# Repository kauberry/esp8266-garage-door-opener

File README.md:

# esp8266-garage-door-opener
An IoT garage door opener using MQTT for status reporting and web api's for control functions

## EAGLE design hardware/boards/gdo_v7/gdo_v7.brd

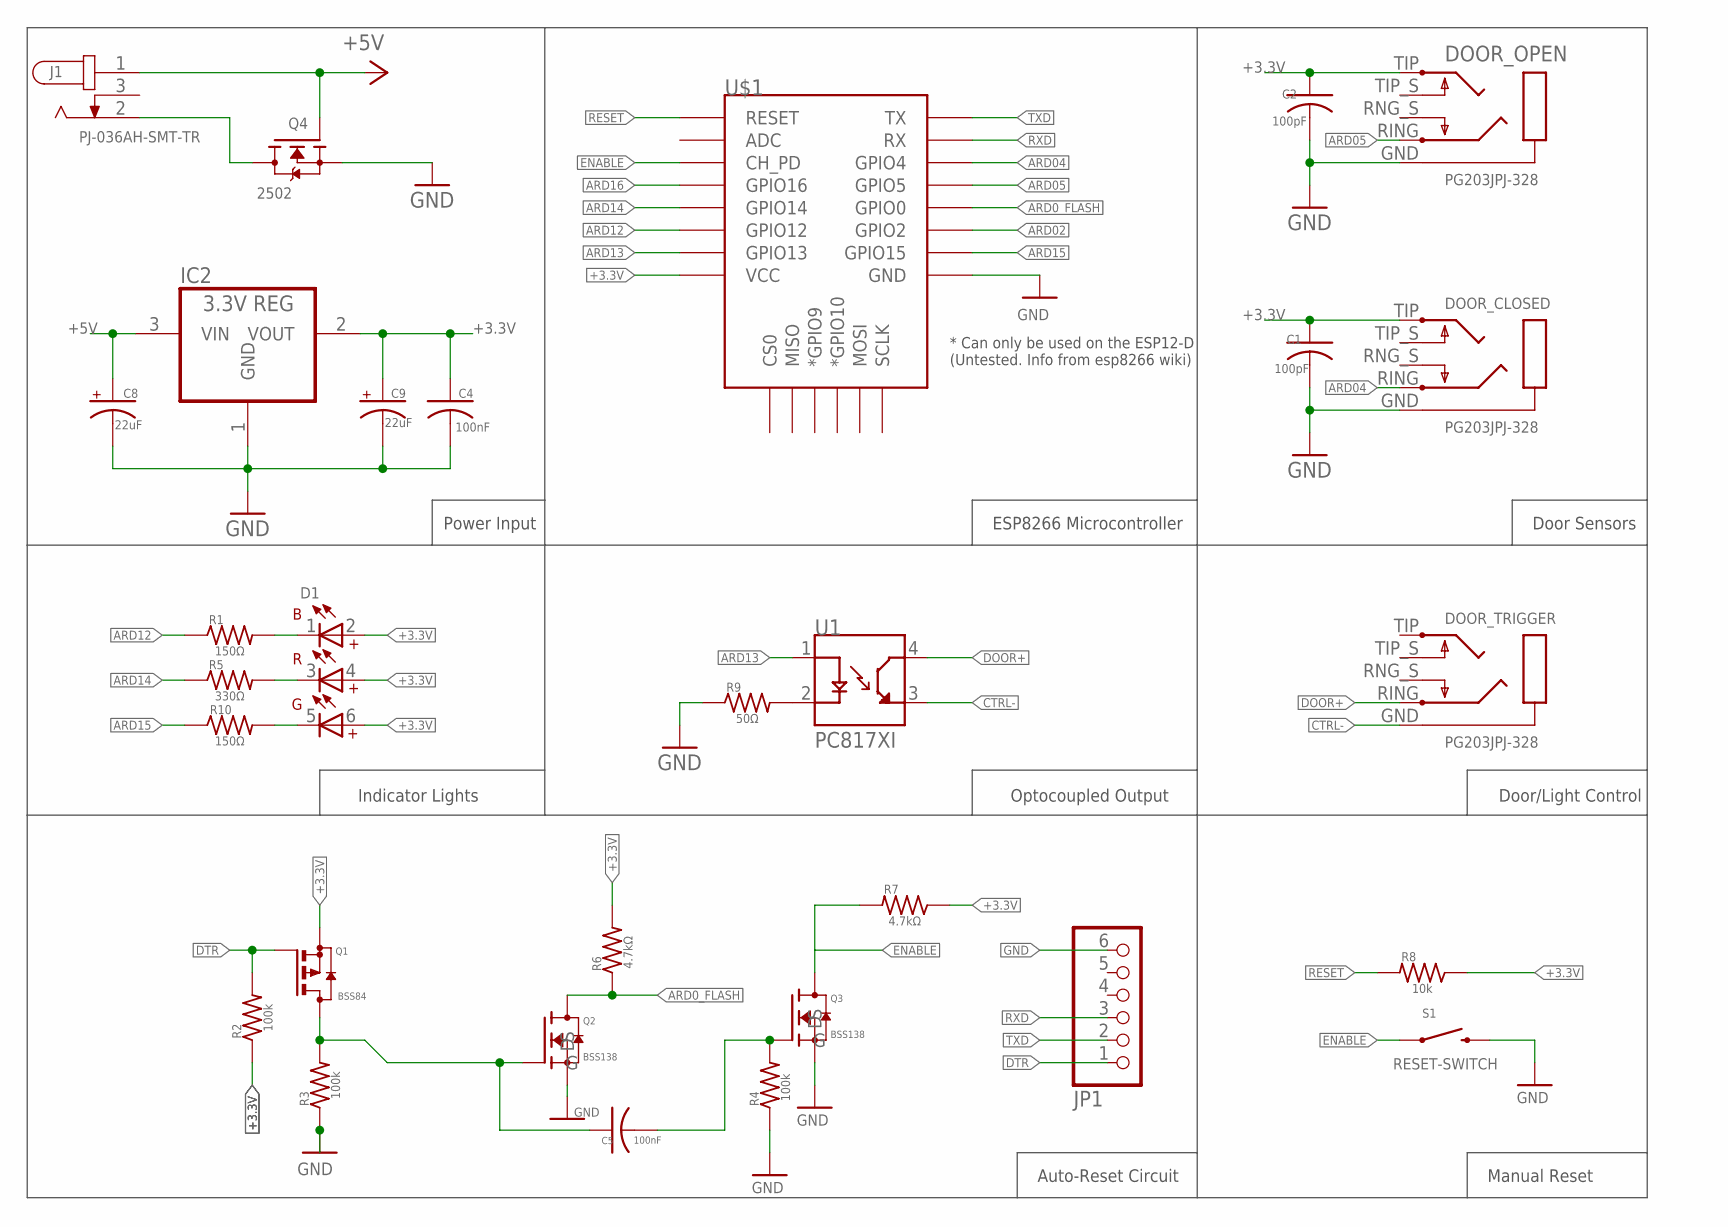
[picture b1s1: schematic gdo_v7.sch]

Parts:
C1, C2: 100pF; C0805
C4, C5: 100nF; C0805
C8, C9: 22uF; EIA3216
D1: WL-SFTW_5050_PLCC6_150505M173300; WL-SFTW_5050_PLCC6
DOOR_CLOSED: PG203JPJ-328; PG203J
DOOR_OPEN: PG203JPJ-328; PG203J
DOOR_TRIGGER: PG203JPJ-328; PG203J
IC2: 3.3V REG; SOT223
J1: PJ-036AH-SMT-TR; CUI_PJ-036AH-SMT-TR
JP1: PINHD-1X6; 1X06
Q1: BSS84; SOT23
Q2, Q3: BSS138
Q4: 2502; SOT23
R1, R10: 150Ω; R0805
R2, R3, R4: 100k; R0805
R5: 330Ω; R0805
R6, R7: 4.7kΩ; R0805
R8: 10k; R0805
R9: 50Ω; R0805
S1: RESET-SWITCH; TACTILE-SWITCH-1101NE
U1: PC817XI; SOIC254P975X460-4N
U$1: ESP12ESMD; ESP12E-SMD

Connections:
+3.3V: C1.1, C2.1, C4.1, C9.A (+), D1.2, D1.4, D1.6, DOOR_CLOSED.TIP (5), DOOR_OPEN.TIP (5), IC2.2 (VOUT), Q1.2 (S), R2.1, R6.2, R7.1, R8.1, U$1.VCC
+5V: C8.A (+), IC2.3 (VIN), J1.1, Q4.1 (G)
ARD0_FLASH: Q2.D, R6.1, U$1.GPIO0
ARD02: U$1.GPIO2
ARD04: DOOR_CLOSED.RING (2), U$1.GPIO4
ARD05: DOOR_OPEN.RING (2), U$1.GPIO5
ARD12: R1.1, U$1.GPIO12
ARD13: U1.1 (A), U$1.GPIO13
ARD14: R5.1, U$1.GPIO14
ARD15: R10.1, U$1.GPIO15
ARD16: U$1.GPIO16
CTRL-: DOOR_TRIGGER.GND (1), U1.3 (ET)
DOOR+: DOOR_TRIGGER.RING (2), U1.4 (CT)
DTR: JP1.1, Q1.1 (G), R2.2
ENABLE: Q3.D, R7.2, S1.P$1 (1), U$1.CH_PD
GND: C1.2, C2.2, C4.2, C8.C (-), C9.C (-), DOOR_CLOSED.GND (1), DOOR_OPEN.GND (1), IC2.1 (GND), JP1.6, Q2.S, Q3.S, Q4.2 (S), R3.1, R4.1, R9.1, S1.P$2 (2), U$1.GND
unnamed: J1.2, Q4.3 (D)
unnamed: C5.2, Q3.G, R4.2
unnamed: D1.1, R1.2
unnamed: D1.3, R5.2
unnamed: C5.1, Q1.3 (D), Q2.G, R3.2
unnamed: R9.2, U1.2 (C)
unnamed: D1.5, R10.2
RESET: R8.2, U$1.RESET
RXD: JP1.3, U$1.RXD0 (RX)
TXD: JP1.2, U$1.TXD0 (TX)

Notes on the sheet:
Power Input
ESP8266 Microcontroller
Optocoupled Output
Door Sensors
Door/Light Control
Auto-Reset Circuit
Manual Reset
Indicator Lights

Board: 2 copper layers, 30 parts (5 on the bottom side), 24 nets, no tracks yet.

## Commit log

2016-04-18 Trying to get MQTT to work at the same time as the REST server
2016-04-20 Adding initial Eagle files
2016-04-20 Minor edits
2016-04-21 Adding sensor mount Sketchup file
2016-04-25 Updating model files for mounting hardware
2016-04-25 Adding initial EagleCAD files for controller board
2016-04-25 Updating routing and layout
2016-04-26 Mostly final board design
2016-04-26 Closer to final board design
2016-04-26 Added dimensions to board layout
2016-04-26 Added first cut at a 3D printed enclosure
2016-04-26 Updated sensor and magnet mounts
2016-04-27 Added resistor for optocoupler inputs
2016-04-29 More board tweaks
2016-05-01 Updated main codebase to remove crappy REST server module
2016-05-11 Replacing 3.5mm Jack with SMT design
2016-05-11 Redesigning main board for more SMT components
2016-05-11 Switching over to ESP-12e
2016-05-13 Updating main board files
2016-05-15 Finalized version of board for OshPark
2016-05-16 Fixing bad pull down connection in auto-reset circuit
2016-05-31 Added pullup resistor for GPIO0
2016-06-15 Fixing Board issues
2016-06-20 Updating board to better match prototype design
2016-06-20 Fixing state indicator LED's to update immediately on startup Increasing delay between mandatory reporting intervals for temperature
2016-06-21 Tweaked power rails and updated descriptive text before sending to fab
2016-06-21 Adding in OTA update capability
2016-06-22 Added initial implementation of OTA update functionality
2016-07-12 Board Design: Changed power supply buffer caps from 10µF to 22µF. Flipped Status LED connections for proper polarity. Added 10kΩ on GPIO15 to match with adapter board design on prototype.
2016-07-12 Software: More fixes for configuration logic. Removed SPIFFS conf file loading for now. Added code to handle the additional external temperature probe
2016-08-11 Trying to clear up double reporting on open
2016-11-10 Updates to mounting hardware for better fit and clearance
2017-11-30 Pushing updated hardware and Eagle component libraries
2020-02-09 First commit of version 7 board schematic
2020-03-09 Initial commit of the v7 board designs

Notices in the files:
parts and their libraries:
SparkFun-Capacitors: Licensing: CC v3.0 Share-Alike You are welcome to use this library for commercial purposes.
Eagle_WL-SFTW_rev19c: Copyright: Würth Elektronik
